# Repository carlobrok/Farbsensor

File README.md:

# RGB Farbsensor

Analoger RGB Farbsensor entwickelt für den Robo-Cup Rescue Line.

Library für den Sensor: https://github.com/carlobrok/Sensorleiste

### Eigenschaften

* 10,5 mm x 17,7 mm
* 6 Pins
* M3 Loch
* Sehr helle RGB LED
* Analoge Spannung als Helligkeitswert
* SMD-Komponenten
* Günstig

### Pinbelegung

Pin  | Funktion
-----|---------
GND  | Ground / Masse
5V   | 5V Photodiode
SEN  | Spannung der Photodiode
R    | 5V Rote LED (50 mA)
G    | 5V Grüne LED (35 mA)
B    | 5V Blaue LED (30 mA)

### Bauteile

Bauteil | Menge |   Name / Link
-------|--|---------------
LED  | 1 | [Nichia NSSM124DT](https://www.leds.de/nichia-nssm124dt-smd-led-rgb-30201.html)
Photodiode | 1 | [SFH-2711](https://www.mouser.de/ProductDetail/OSRAM-Opto-Semiconductors/SFH-2711?qs=%252BEew9%252B0nqrDd5IpctorHnA==)
Transistor | 1 | [BCW32](https://www.digikey.de/product-detail/de/on-semiconductor/BCW32LT1G/BCW32LT1GOSCT-ND/2704971)
Pins | 1 | [3x2 Steckleiste](https://www.digikey.de/product-detail/de/amphenol-icc-fci/67997-206HLF/609-3234-ND/1878491)
R1 | 1 | [100k](https://www.digikey.de/product-detail/de/yageo/RC0603FR-07100KL/311-100KHRCT-ND/729836)
R2 | 1 | [147](https://www.digikey.de/product-detail/de/yageo/RC0603FR-07147RL/311-147HRCT-ND/729897)
R3/R4 | 2 | [100](https://www.digikey.de/product-detail/de/yageo/RT0603BRD07100RL/YAG1497CT-ND/5138945)

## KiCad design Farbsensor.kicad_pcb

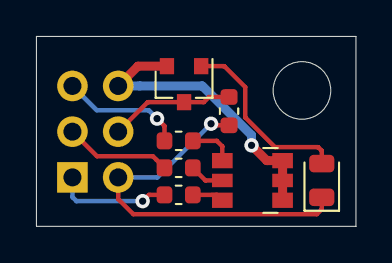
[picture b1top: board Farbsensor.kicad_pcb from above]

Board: 2 copper layers, 17.8 x 10.5 mm, 9 parts (1 on the bottom side), 10 nets.

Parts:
D1: SFH2711; D_0805_2012Metric
D2: NSSM124DT; LED_NSSM124D_4.5x3.05mm
H1: MountingHole; MountingHole_3.2mm_M3_DIN965
J1: Conn_02x03_Odd_Even; PinHeader_2x03_P2.54mm_Vertical
Q1: BCW32; SOT-23
R1: 100k; R_0603_1608Metric
R2: 147; R_0603_1608Metric
R3, R4: 100; R_0603_1608Metric

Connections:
+5V: D1.1, J1.2, R1.1
/B: D2.6, R2.2
/G: D2.5, R3.2
/LED_B: J1.1, R2.1
/LED_G: J1.3, R3.1
/LED_R: J1.5, R4.1
/R: D2.4, R4.2
/SEN: J1.4, Q1.3, R1.2
GND: D2.1, D2.2, D2.3, J1.6, Q1.2
unnamed: D1.2, Q1.1

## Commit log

2019-08-22 Add KiCad project
2019-08-22 changed pcb layout, switched pin assignment
2019-08-24 Ignore images
2019-08-24 ignore *.sch-bak
2019-08-24 changed pin header assignment
2019-08-24 changed pin header assignment, moved resistor
2019-08-24 Added outline drawing of LED
2019-09-13 Layout überarbeitet, Beschriftungsfehler behoben
2019-09-29 Beschriftung geändert
2019-10-14 Update LICENSE
